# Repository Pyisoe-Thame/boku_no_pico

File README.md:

# Boku no Pico

## Introduction
This repository contains the design files and documentation for Boku no Pico (RP2040) development board, which is a variant of ARM Cortex-M0+ Raspberry Pi Pico. This board is tailored to enhance development for embedded systems enthusiasts by adding essential features and simplifying debugging and prototyping.

---

## Features
- Powered by the Raspberry Pi RP2040 microcontroller.
- Standard 4-pin SWD and I2C headers 
- USB-C connector for modern connectivity.
- Application of robustment enhancing techniques.
- Compact, breadboard-friendly form factor.

---

## Schematic and PCB Design
The hardware design was created using **KiCad**. The following files are included:
- **Schematic**: `RP2040_DevBoard.kicad_sch`
- **PCB layout**: `RP2040_DevBoard.kicad_pcb`

### Folder Structure
- `BOM/`: Bill of Materials for the components used.
- `PCB/`: Gerber files, Drill files and PaP files.
- `images/`: Board images in 3D but no rendered.

---

## How to Use
### Hardware Setup
1. Assembly the PCB by handing the files inside BOM and PCB folders to a PCB manufacturer such as PCBHero or JLCPCB.
2. Hand-solder manually the pin headers or the way you want (e.g. sockets, wires)
3. Use a 4-pin SWD debugger (e.g., J-Link or Picoprobe) or Arm connector tag for flashing firmware.

### Programming
- Use the official Raspberry Pi Pico SDK for development.
- Alternatively, program using MicroPython or CircuitPython.

---

## Getting Started
1. Clone this repository:
   ```bash
   git clone https://github.com/Pyisoe-Thame/boku_no_pico.git

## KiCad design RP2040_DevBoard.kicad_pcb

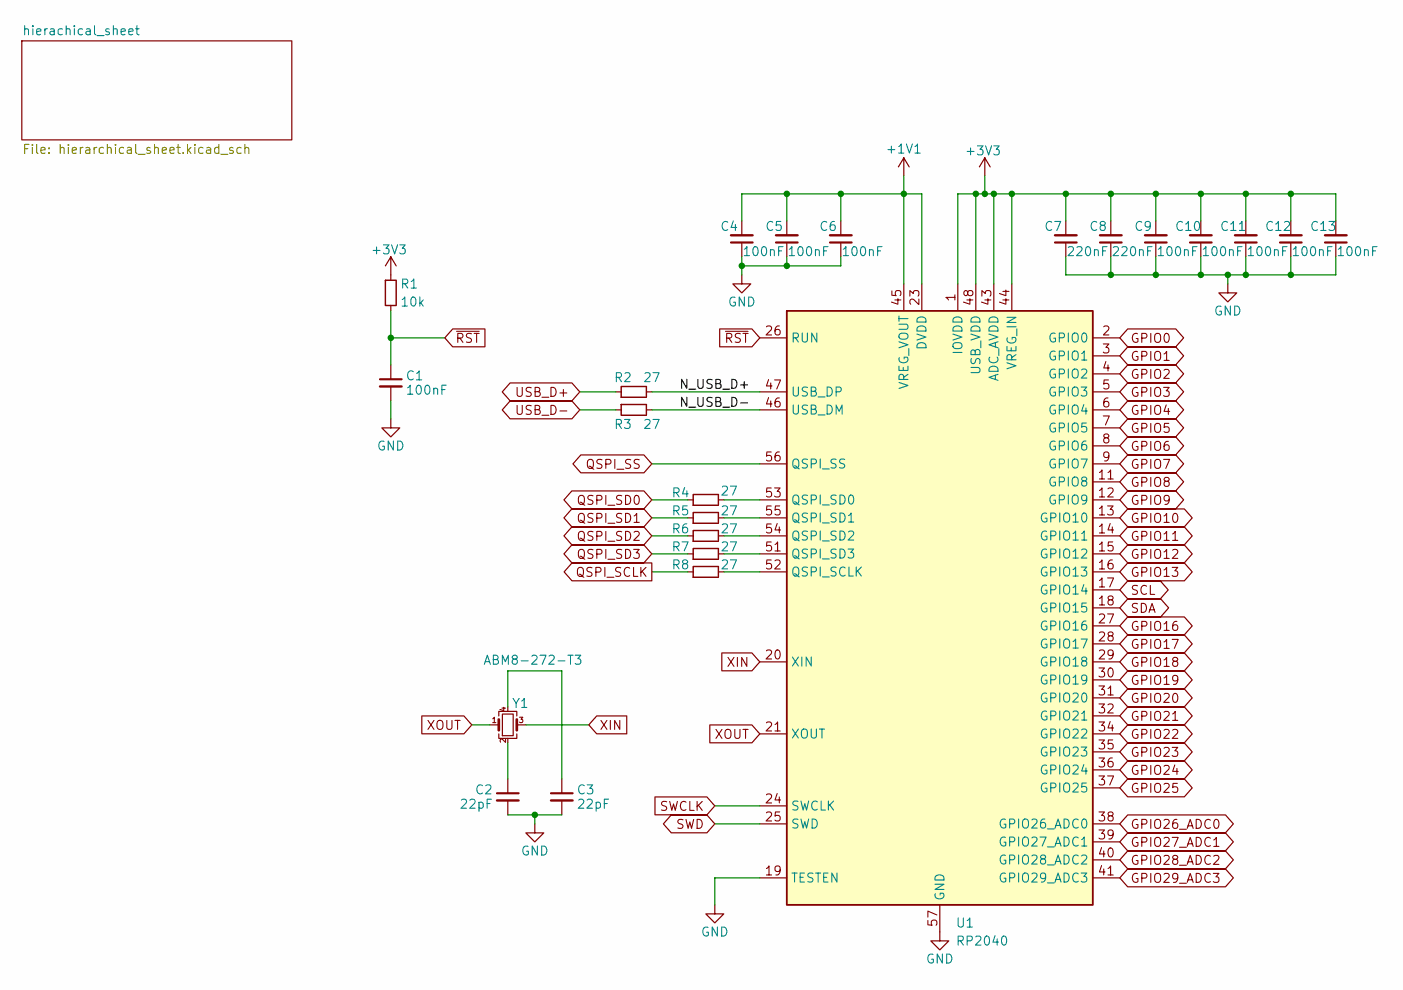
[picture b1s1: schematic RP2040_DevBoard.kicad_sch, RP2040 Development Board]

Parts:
C1, C4, C5, C6, C9, C10, C11, C12, C13: 100nF; C_0402_1005Metric
C2, C3: 22pF; C_0402_1005Metric
C7, C8: 220nF; C_0402_1005Metric
R1: 10k; R_0402_1005Metric
R2, R3, R4, R5, R6, R7, R8: 27; R_0402_1005Metric
U1: RP2040; QFN-56-1EP_7x7mm_P0.4mm_EP4x4mm
Y1: ABM8-272-T3; Crystal_SMD_Abracon_ABM8G-4Pin_3.2x2.5mm

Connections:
+1V1: C4.2, C5.2, C6.2, U1.23 (DVDD), U1.45 (VREG_VOUT), U1.50 (DVDD)
+3V3: C7.2, C8.2, C9.2, C10.2, C11.2, C12.2, C13.2, R1.1, U1.1 (IOVDD), U1.10 (IOVDD), U1.22 (IOVDD), U1.33 (IOVDD), U1.42 (IOVDD), U1.43 (ADC_AVDD), U1.44 (VREG_IN), U1.48 (USB_VDD), U1.49 (IOVDD); also elsewhere on the board
/N_USB_D+: R2.2, U1.47 (USB_DP)
/N_USB_D-: R3.2, U1.46 (USB_DM)
GND: C1.2, C2.2, C3.2, C4.1, C5.1, C6.1, C7.1, C8.1, C9.1, C10.1, C11.1, C12.1, C13.1, U1.19 (TESTEN), U1.57 (GND); also elsewhere on the board
GPIO0: U1.2 (GPIO0); also elsewhere on the board
GPIO1: U1.3 (GPIO1); also elsewhere on the board
GPIO2: U1.4 (GPIO2); also elsewhere on the board
GPIO3: U1.5 (GPIO3); also elsewhere on the board
GPIO4: U1.6 (GPIO4); also elsewhere on the board
GPIO5: U1.7 (GPIO5); also elsewhere on the board
GPIO6: U1.8 (GPIO6); also elsewhere on the board
GPIO7: U1.9 (GPIO7); also elsewhere on the board
GPIO8: U1.11 (GPIO8); also elsewhere on the board
GPIO9: U1.12 (GPIO9); also elsewhere on the board
GPIO10: U1.13 (GPIO10); also elsewhere on the board
GPIO11: U1.14 (GPIO11); also elsewhere on the board
GPIO12: U1.15 (GPIO12); also elsewhere on the board
GPIO13: U1.16 (GPIO13); also elsewhere on the board
GPIO16: U1.27 (GPIO16); also elsewhere on the board
GPIO17: U1.28 (GPIO17); also elsewhere on the board
GPIO18: U1.29 (GPIO18); also elsewhere on the board
GPIO19: U1.30 (GPIO19); also elsewhere on the board
GPIO20: U1.31 (GPIO20); also elsewhere on the board
GPIO21: U1.32 (GPIO21); also elsewhere on the board
GPIO22: U1.34 (GPIO22); also elsewhere on the board
GPIO23: U1.35 (GPIO23); also elsewhere on the board
GPIO24: U1.36 (GPIO24); also elsewhere on the board
GPIO25: U1.37 (GPIO25); also elsewhere on the board
GPIO26_ADC0: U1.38 (GPIO26_ADC0); also elsewhere on the board
GPIO27_ADC1: U1.39 (GPIO27_ADC1); also elsewhere on the board
GPIO28_ADC2: U1.40 (GPIO28_ADC2); also elsewhere on the board
GPIO29_ADC3: U1.41 (GPIO29_ADC3); also elsewhere on the board
unnamed: C2.1, Y1.2
unnamed: C3.1, Y1.4
unnamed: R8.2, U1.52 (QSPI_SCLK)
unnamed: R4.2, U1.53 (QSPI_SD0)
unnamed: R5.2, U1.55 (QSPI_SD1)
unnamed: R6.2, U1.54 (QSPI_SD2)
unnamed: R7.2, U1.51 (QSPI_SD3)
QSPI_SCLK: R8.1; also elsewhere on the board
QSPI_SD0: R4.1; also elsewhere on the board
QSPI_SD1: R5.1; also elsewhere on the board
QSPI_SD2: R6.1; also elsewhere on the board
QSPI_SD3: R7.1; also elsewhere on the board
QSPI_SS: U1.56 (QSPI_SS); also elsewhere on the board
SCL: U1.17 (GPIO14); also elsewhere on the board
SDA: U1.18 (GPIO15); also elsewhere on the board
SWCLK: U1.24 (SWCLK); also elsewhere on the board
SWD: U1.25 (SWD); also elsewhere on the board
USB_D+: R2.1; also elsewhere on the board
USB_D-: R3.1; also elsewhere on the board
XIN: U1.20 (XIN), Y1.3
XOUT: U1.21 (XOUT), Y1.1
~RST: C1.1, R1.2, U1.26 (RUN); also elsewhere on the board

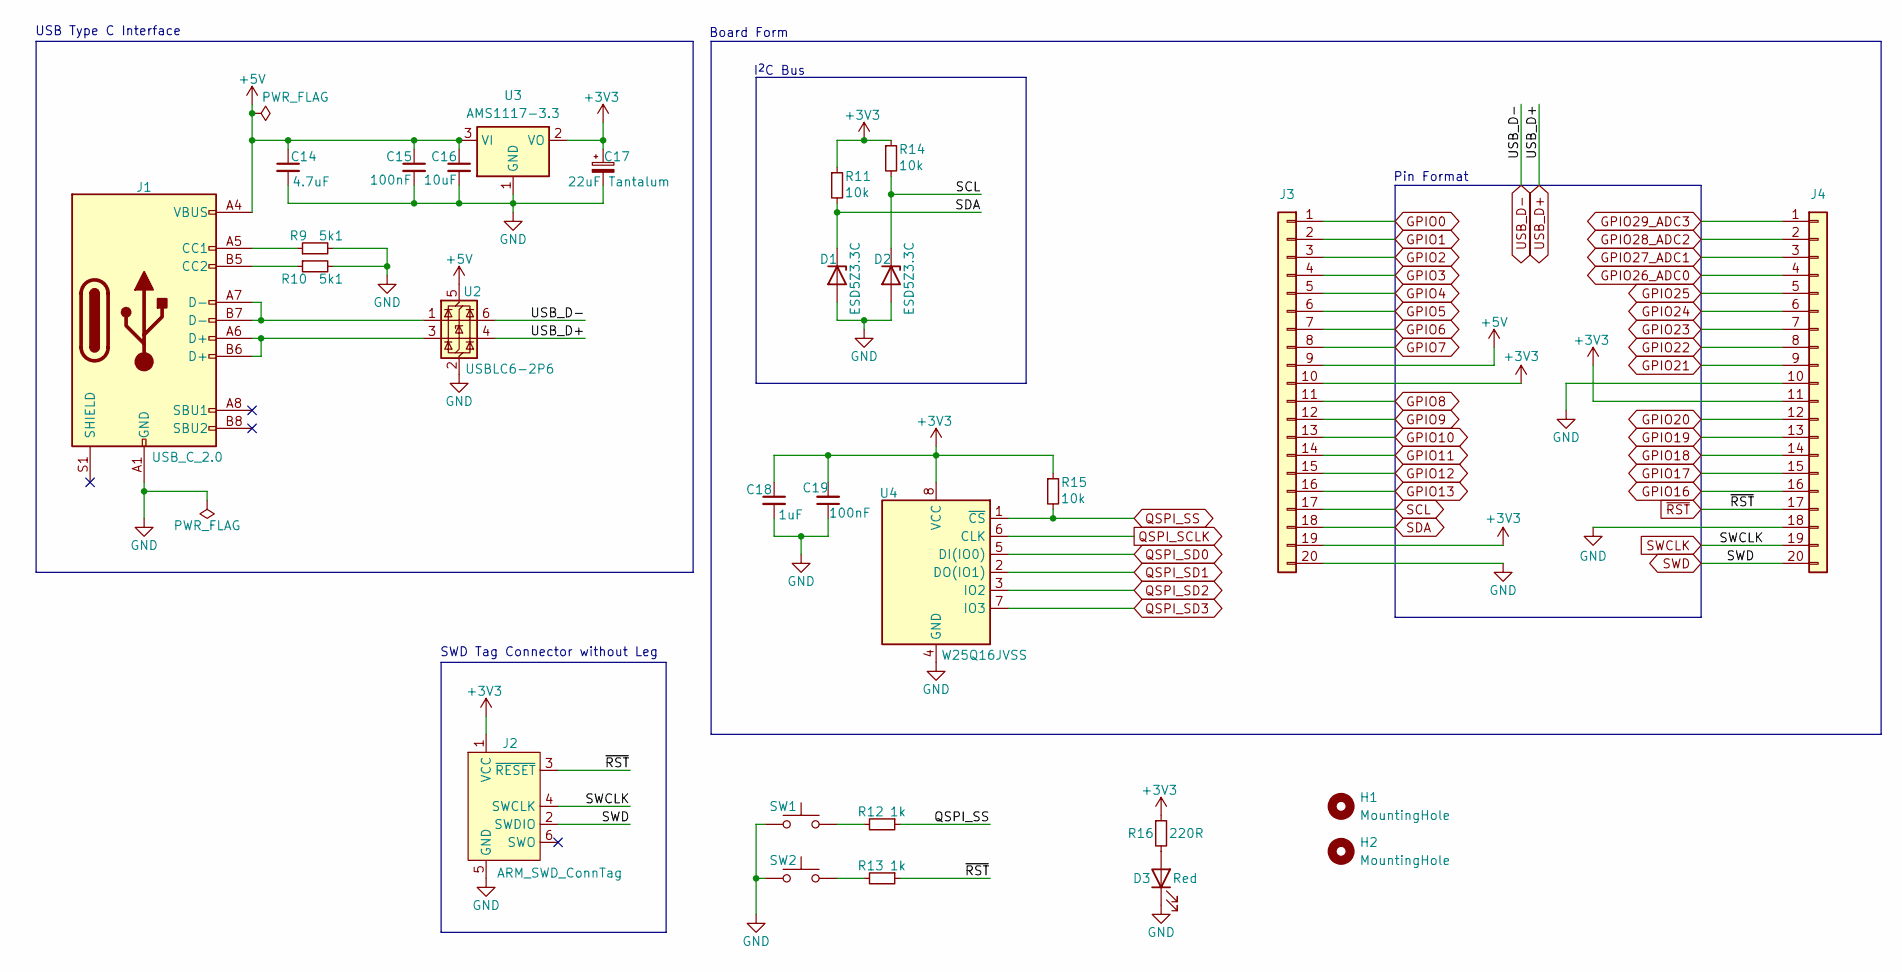
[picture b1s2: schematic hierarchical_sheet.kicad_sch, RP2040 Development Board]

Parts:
C14: 4.7uF; C_0603_1608Metric
C15, C19: 100nF; C_0402_1005Metric
C16: 10uF; C_0805_2012Metric
C17: 22uF; CP_EIA-3216-18_Kemet-A
C18: 1uF; C_0402_1005Metric
D1, D2: ESD5Z3.3C; D_SOD-523
D3: Red; LED_0603_1608Metric
H1, H2: MountingHole; MountingHole_2.2mm_M2
J1: USB_C_2.0; USB_C_Receptacle_HRO_TYPE-C-31-M-12
J2: ARM_SWD_ConnTag; Tag-Connect_TC2030-IDC-NL_2x03_P1.27mm_Vertical
J3, J4: Conn_01x20; PinHeader_1x20_P2.54mm_Vertical
R9, R10: 5k1; R_0402_1005Metric
R11, R14, R15: 10k; R_0402_1005Metric
R12, R13: 1k; R_0603_1608Metric
R16: 220R; R_0603_1608Metric
SW1, SW2: SW_Push; SW_PUSH_6mm
U2: USBLC6-2P6; SOT-563
U3: AMS1117-3.3; SOT-223-3_TabPin2
U4: W25Q16JVSS; SOIC-8_5.275x5.275mm_P1.27mm

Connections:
+3V3: C17.1, C18.1, C19.2, J2.1 (VCC), J3.10, J3.19, J4.11, R11.1, R14.1, R15.1, R16.1, U3.2 (VO), U4.8 (VCC); also elsewhere on the board
+5V: C14.1, C15.1, C16.1, J1.A4 (VBUS), J1.A9 (VBUS), J1.B4 (VBUS), J1.B9 (VBUS), J3.9, U2.5 (VBUS), U3.3 (VI)
GND: C14.2, C15.2, C16.2, C17.2, C18.2, C19.1, D1.2 (A), D2.2 (A), D3.1 (K), J1.A1 (GND), J1.A12 (GND), J1.B1 (GND), J1.B12 (GND), J2.5 (GND), J3.20, J4.10, J4.18, R9.2, R10.2, SW1.1, SW2.1, U2.2 (GND), U3.1 (GND), U4.4 (GND); also elsewhere on the board
GPIO0: J3.1; also elsewhere on the board
GPIO1: J3.2; also elsewhere on the board
GPIO2: J3.3; also elsewhere on the board
GPIO3: J3.4; also elsewhere on the board
GPIO4: J3.5; also elsewhere on the board
GPIO5: J3.6; also elsewhere on the board
GPIO6: J3.7; also elsewhere on the board
GPIO7: J3.8; also elsewhere on the board
GPIO8: J3.11; also elsewhere on the board
GPIO9: J3.12; also elsewhere on the board
GPIO10: J3.13; also elsewhere on the board
GPIO11: J3.14; also elsewhere on the board
GPIO12: J3.15; also elsewhere on the board
GPIO13: J3.16; also elsewhere on the board
GPIO16: J4.16; also elsewhere on the board
GPIO17: J4.15; also elsewhere on the board
GPIO18: J4.14; also elsewhere on the board
GPIO19: J4.13; also elsewhere on the board
GPIO20: J4.12; also elsewhere on the board
GPIO21: J4.9; also elsewhere on the board
GPIO22: J4.8; also elsewhere on the board
GPIO23: J4.7; also elsewhere on the board
GPIO24: J4.6; also elsewhere on the board
GPIO25: J4.5; also elsewhere on the board
GPIO26_ADC0: J4.4; also elsewhere on the board
GPIO27_ADC1: J4.3; also elsewhere on the board
GPIO28_ADC2: J4.2; also elsewhere on the board
GPIO29_ADC3: J4.1; also elsewhere on the board
unnamed: D3.2 (A), R16.2
unnamed: J1.A5 (CC1), R9.1
unnamed: J1.B5 (CC2), R10.1
unnamed: J1.A6 (D+), J1.B6 (D+), U2.3 (I/O2)
unnamed: J1.A7 (D-), J1.B7 (D-), U2.1 (I/O1)
unnamed: R12.2, SW1.2
unnamed: R13.2, SW2.2
QSPI_SCLK: U4.6 (CLK); also elsewhere on the board
QSPI_SD0: U4.5 (DI(IO0)); also elsewhere on the board
QSPI_SD1: U4.2 (DO(IO1)); also elsewhere on the board
QSPI_SD2: U4.3 (IO2); also elsewhere on the board
QSPI_SD3: U4.7 (IO3); also elsewhere on the board
QSPI_SS: R12.1, R15.2, U4.1 (~CS); also elsewhere on the board
SCL: D2.1 (K), J3.17, R14.2; also elsewhere on the board
SDA: D1.1 (K), J3.18, R11.2; also elsewhere on the board
SWCLK: J2.4 (SWCLK), J4.19; also elsewhere on the board
SWD: J2.2 (SWDIO), J4.20; also elsewhere on the board
USB_D+: U2.4 (I/O2); also elsewhere on the board
USB_D-: U2.6 (I/O1); also elsewhere on the board
~RST: J2.3 (~RESET), J4.17, R13.1; also elsewhere on the board

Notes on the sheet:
USB Type C Interface
Board Form
I^{2}C Bus
SWD Tag Connector without Leg
Pin Format

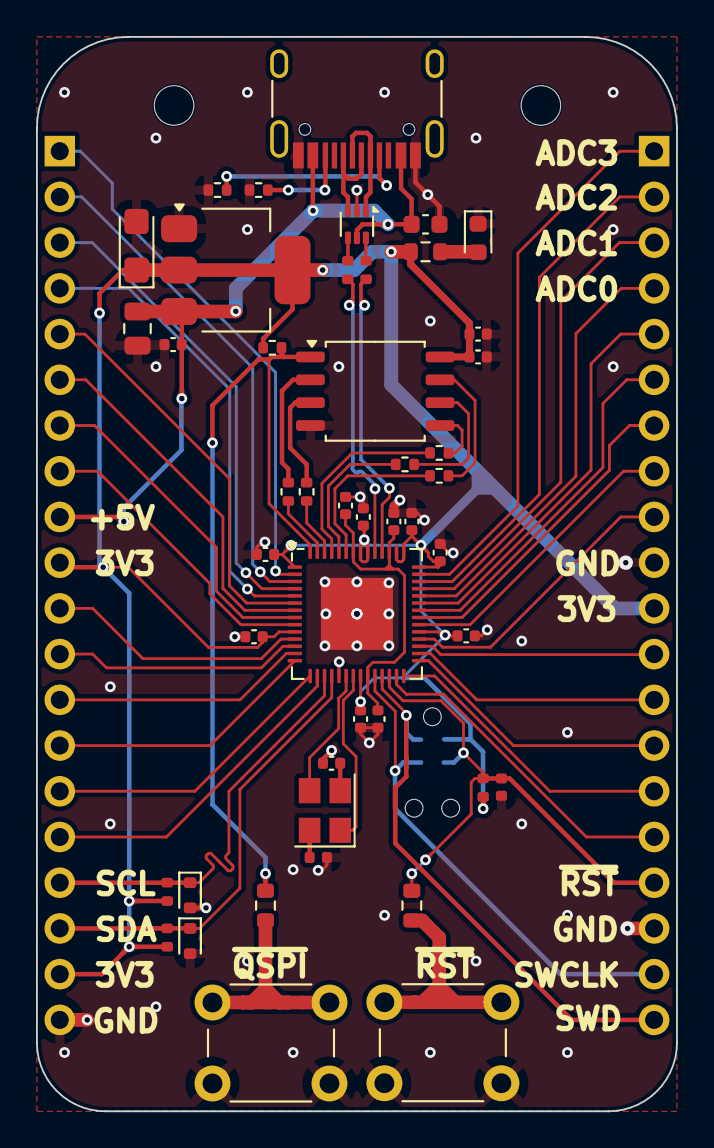
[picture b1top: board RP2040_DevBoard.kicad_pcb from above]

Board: 4 copper layers, 35.6 x 59.7 mm, 51 parts (1 on the bottom side), 63 nets.

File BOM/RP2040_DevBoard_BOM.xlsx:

Designator | Label | LCSC Part # | Mfr. Part # | Manufacturer | Footprint | Quantity | Price | Stock Minimum | Cost | Actual Cost | 5 Boards Cost
C1, C4, C5, C6, C9, 10, C11, C12, C13, C15, C19 | 100nF | C392963 | TCC0402X7R104K160AT | CCTC | C_0402_1005Metric | 11 | 0.0009 | 100 | 0.0099 | 0.09 | 0.0495
C7, C8 | 220nF | C7503518 | CGA0402X5R224K100GT | HRE | C_0402_1005Metric | 2 | 0.0014 | 100 | 0.0028 | 0.14 | 0.014
C2, C3 | 22pF | C2175872 | CC0402JRNPO7BN220 | YAGEO | C_0402_1005Metric | 2 | 0.0011 | 100 | 0.0022 | 0.11 | 0.011
C18 | 1uF | C5142580 | TCC0402X5R105K160AT | CCTC | C_0402_1005Metric | 1 | 0.002 | 100 | 0.002 | 0.2 | 0.01
C14 | 4.7uF | C6119855 | CGA0603X5R475K160JT | HRE | C_0603_1608Metric | 1 | 0.0058 | 100 | 0.0058 | 0.58 | 0.029
C16 | 10uF | C1713 | CL21A106KOQNNNE | Samsung Electro-Mechanics | C_0805_2012Metric | 1 | 0.0078 | 20 | 0.0078 | 0.156 | 0.039
C17 | 22uF | C124838 | TC212A226M010B | Sunlord | CP_EIA-3216-18_Kemet-A | 1 | 0.0928 | 5 | 0.0928 | 0.464 | 0.464
D1, D2 | ESD5Z3.3C | C5180227 | ESD5Z3.3C-ES | ElecSuper | D_SOD-523 | 2 | 0.0132 | 5 | 0.0264 | 0.066 | 0.132
D3 | Red | C965799 | XL-1608SURC-06 | XINGLIGHT | LED_0603_1608Metric | 1 | 0.003 | 100 | 0.003 | 0.3 | 0.015
J1 | USB_C_2.0 | C165948 | TYPE-C-31-M-12 | Korean Hroparts Elec | USB_C_Receptacle_HRO_TYPE-C-31-M-12 | 1 | 0.1552 | 5 | 0.1552 | 0.776 | 0.776
R1, R11, R14, R15 | 10k | C3017497 | SCR0402J10K | VO | R_0402_1005Metric | 2 | 0.0004 | 100 | 0.0008 | 0.04 | 0.004
R2, R3, R4, R5, R6, R7, R8 | 27R | C2929914 | FRC0402J270TS | FOJAN | R_0402_1005Metric | 7 | 0.0003 | 100 | 0.0021 | 0.03 | 0.0105
R9, R10 | 5k1 | C23186 | 0603WAF5101T5E | UNI-ROYAL(Uniroyal Elec) | R_0402_1005Metric | 2 | 0.001 | 100 | 0.002 | 0.1 | 0.01
R12, R13 | 1k | C881173 | CR0603J1K00P05Z | Ever Ohms Tech | R_0603_1608Metric | 2 | 0.0013 | 100 | 0.0026 | 0.13 | 0.013
R16 | 220R | C22962 | 0603WAF2200T5E | UNI-ROYAL(Uniroyal Elec) | R_0603_1608Metric | 1 | 0.001 | 100 | 0.001 | 0.1 | 0.005
SW1, SW2 | SW_Push | C29781309 | SMG-01-H055A1 | SM Switch | SW_PUSH_6mm | 2 | 0.0154 | 20 | 0.0308 | 0.308 | 0.154
U1 | RP2040 | C2040 | RP2040 | Raspberry Pi | QFN-56-1EP_7x7mm_P0.4mm_EP4x4mm_ThermalVias | 1 | 1.0357 | 1 | 1.0357 | 1.0357 | 5.1785
U2 | USBLC6-2P6 | C19188420 | LM-USBLC6-2P6 | Leiditech | SOT-563 | 1 | 0.0516 | 5 | 0.0516 | 0.258 | 0.258
U3 | AMS1117-3.3 | C347222 | AMS1117-3.3 | UMW(Youtai Semiconductor Co., Ltd.) | SOT-223-3_TabPin2 | 1 | 0.0335 | 5 | 0.0335 | 0.1675 | 0.1675
U4 | W25Q16JVSS | C82317 | W25Q16JVSSIQ | Winbond Elec | SOIC-8_5.275x5.275mm_P1.27mm | 1 | 0.2263 | 5 | 0.2263 | 1.1315 | 1.1315
Y1 | ABM8-272-T3 | C20625731 | ABM8-272-T3 | Abracon LLC | Crystal_SMD_Abracon_ABM8G-4Pin_3.2x2.5mm | 1 | 0.4899 | 1 | 0.4899 | 0.4899 | 2.4495
Total |  |  |  |  |  |  |  |  | 2.1842 | 6.6726 | 10.921
 |  | Note: pin headers excluded

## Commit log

2024-11-26 all project files
